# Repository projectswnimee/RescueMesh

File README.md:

<div align="center">

# RescueMesh

**ESP32 and LoRa emergency messaging for flood and disaster response**

**Semi-finalist — SL IoT competition, Sri Lanka**

</div>

<p align="center">
  
  <br>
  <sub>Original prototype photograph supplied by project collaborator Nimesha Nanayakkara. Click to view full size.</sub>
</p>

RescueMesh explores how battery-powered nodes can exchange SOS messages when
normal connectivity is unavailable. ESP32 controllers communicate through
AS32-TTL-100 LoRa radios, with progressive experiments covering broadcast,
relay forwarding, duplicate suppression, TTL and gateway uploads.

This is Nimesha Nanayakkara's maintained copy of the collaborative project.
The [original team repository](https://github.com/HiranGeeth/RescueMesh-Disaster-Rescue_Long-Range-Communication-System),
original MIT licence and hardware-author credits are preserved through explicit
[source attribution](ATTRIBUTION.md).

## System overview

```text
SOS button / Bluetooth input
            ↓
ESP32 field node ↔ LoRa relay nodes ↔ gateway receiver
                                           ↓
                                  Wi-Fi → test backend

Power-path PCB + battery supply + enclosure support the node hardware.
```

The checked-in firmware implements custom messaging over LoRa modules.
An operational LoRaWAN network server and LoRaWAN compliance are not demonstrated.

## Included implementation

| Area | Source and assets |
|---|---|
| Firmware experiments | [test_codes/](test_codes/) — UART, parameter configuration, point-to-point and broadcast messaging |
| Relay behaviour | Deduplication, time windows, TTL, randomized retransmission and rebroadcast tests |
| User interaction | SOS button handling and Bluetooth-to-node experiments |
| Gateway integration | LoRa reception and Wi-Fi upload to a configurable test endpoint |
| Power electronics | [Power-path circuit](hardware/Power%20Path%20Management%20Circuit/) — KiCad schematic/PCB, circuit image and fabrication PDFs |
| Mechanical design | [Enclosure](hardware/Enclosure/) — Blender, STL, Cura and printer-specific G-code assets |
| Coverage studies | [MATLAB simulations](matlab_simulations/) — terrain, coverage and routing experiments |

## Hardware design previews

<p align="center">

</p>

These are design assets. The power-path and enclosure documentation credits
**Lasindu Viduranga**. The photograph above documents the assembled prototype;
calibrated power measurements and repeatable field-range data still need to
be added with their test conditions.

## Getting started

1. Clone this repository:

   ```bash
   git -c core.longpaths=true clone https://github.com/projectswnimee/RescueMesh.git
   ```

2. Use Arduino IDE with the ESP32 board support installed. Choose the board
   matching your ESP32 development module.
3. Start with [the GPIO/UART test](test_codes/Code_1.0_GPIO_UART_Test/1.0_GPIO_UART_Test.ino).
   Read the selected sketch's pin definitions before connecting the radio.
4. Progress through parameter read/write and point-to-point tests before using
   relay or field-node sketches. Match radio channel and air settings at both ends.
5. For the gateway upload test, copy
   [secrets.example.h](test_codes/Code_1.3.2.1_Gateway_Backend_Upload_Test/Reciever_Code/secrets.example.h)
   to `secrets.h` in the same sketch folder and enter your own Wi-Fi and endpoint
   values. That local file is ignored by Git.
6. Record the sketch, board package version, wiring, settings and serial logs
   with each experiment. Test one transmitter/receiver pair before adding relays.

The original directories and sketch filenames are retained for traceability.
Arduino IDE may offer to create a matching sketch folder for older filenames.

For `matlab_simulations/DEM.m`, set `OPENTOPOGRAPHY_API_KEY` in your local
environment if downloading new terrain data. Do not commit or print the key.

## Evidence and limits

- **Competition:** semi-finalist in the SL IoT competition, Sri Lanka, reported
  by project collaborator Nimesha Nanayakkara. The edition/year and official
  certificate or announcement are pending addition; see [attribution](ATTRIBUTION.md).
- **Radio:** range and power depend on antennas, configuration, environment and
  board design. Source claims such as 3 km or microamp sleep current are not
  presented here as independently measured whole-system results.
- **Security:** the field-node sketch contains a public demonstration key
  whitelist. This does not establish cryptographic authentication or confidentiality;
  an upstream filename containing “Encryption” is not evidence of secure encryption.
- **Readiness:** folder names such as `Production_Firmware` are inherited source
  labels. This copy has not been newly tested on physical hardware, and is not
  a certified emergency-response system.
- **Simulation:** terrain inputs and MATLAB outputs need their own provenance
  and validation; a coverage simulation does not establish field coverage.

## Collaboration and licence

Use branches and pull requests for new contributions. State your engineering
role and attach relevant measurements or design files. Uploading the shared
source does not confer sole authorship of the project.

See [ATTRIBUTION.md](ATTRIBUTION.md) for the source revision, documented
contributors and publication changes. The original [MIT licence](LICENSE)
and its copyright notice are retained unchanged.

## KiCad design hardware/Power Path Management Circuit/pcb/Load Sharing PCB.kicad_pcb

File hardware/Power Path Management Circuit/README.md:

# 🔋 Power Path Management Circuit  
## LiPo Charger + Boost Converter with Load Sharing (5V Output)

---

## 📌 Description
This module implements a **power path management system** that allows a device (e.g., Arduino, ESP32) to be powered while simultaneously charging a LiPo battery.

### ✅ Key Features
- Safe battery charging  
- Automatic load sharing between USB input and battery  
- Stable 5V output using a boost converter  

---

## ⚙️ How It Works
- The **TP4056 module** charges the LiPo battery from a 5V USB input  
- A **P-channel MOSFET (DMP1045U)** controls power flow  

### 🔌 Operation Modes
**When USB is connected:**
- Load is powered directly from USB  
- Battery charges simultaneously  

**When USB is disconnected:**
- Battery supplies power to the load  

- The **MT3608 boost converter** steps battery voltage up to a stable **5V output**

---

## 🧩 Components Used
- TP4056 LiPo Charger Module (with protection)  
- LiPo Battery (3.7V)  
- DMP1045U P-Channel MOSFET  
- SB220 Schottky Diode  
- 10kΩ Resistor  
- MT3608 Boost Converter Module  

---

## 📁 Files Included
- **schematics/** → Circuit diagram files  
- **pcb/** → PCB design files (Gerber, layout)  

---

## 🔌 Input & Output
- **Input:** 5V (USB)  
- **Battery:** 3.7V LiPo  
- **Output:** Regulated 5V  

---

## ⚠️ Notes
- Adjust **Rprog** on TP4056 to set charging current  
- Adjust **MT3608** to get exact 5V output before connecting load  
- Ensure proper heat dissipation for high current usage  

---

## 🧠 Applications
- Arduino & Embedded Systems  
- Portable electronics  
- IoT devices with battery backup  

---

## 👨‍💻 Author
**Lasindu Viduranga**  
📧 wplvidu@gmail.com  

**Team Member**  
Rescue Mesh

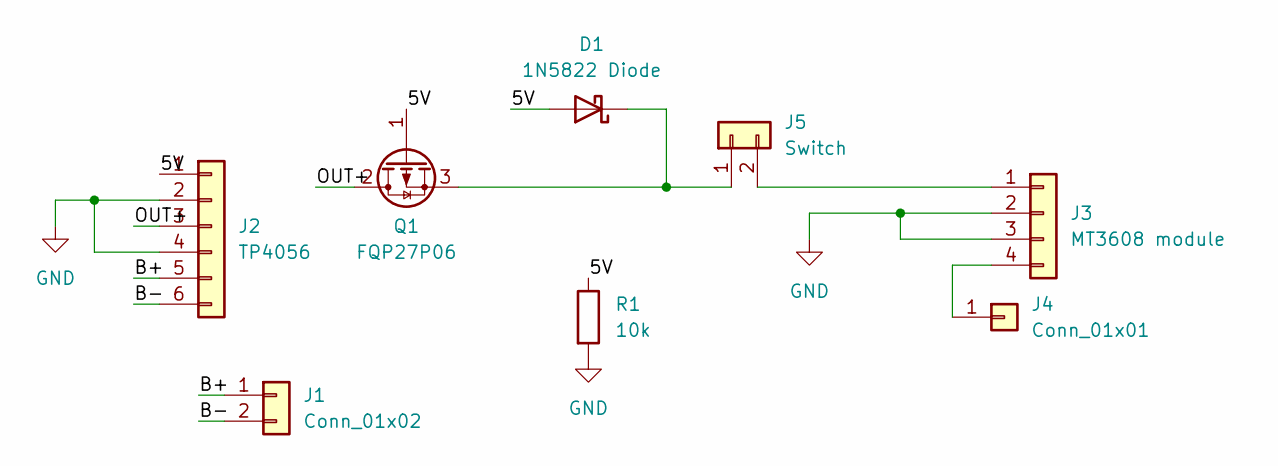
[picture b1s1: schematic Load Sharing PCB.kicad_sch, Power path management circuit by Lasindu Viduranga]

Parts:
D1: 1N5822 Diode; D_DO-201AD_P3.81mm_Vertical_AnodeUp
J1: Conn_01x02; PinHeader_1x02_P2.54mm_Vertical
J2: TP4056; TP4056-18650
J3: MT3608 module; MT3608_module
J4: Conn_01x01; PinHeader_1x01_P2.54mm_Vertical
J5: Switch; PinHeader_1x02_P2.54mm_Horizontal
Q1: FQP27P06; TO-220-3_Vertical
R1: 10k; R_Axial_DIN0207_L6.3mm_D2.5mm_P7.62mm_Horizontal

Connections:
/5V: D1.2 (A), J2.1, Q1.1 (G), R1.1
/B+: J1.1, J2.5
/B-: J1.2, J2.6
/OUT+: J2.3, Q1.2 (D)
GND: J2.2, J2.4, J3.2, J3.3, R1.2
unnamed: D1.1 (K), J5.1, Q1.3 (S)
unnamed: J3.1, J5.2
unnamed: J3.4, J4.1

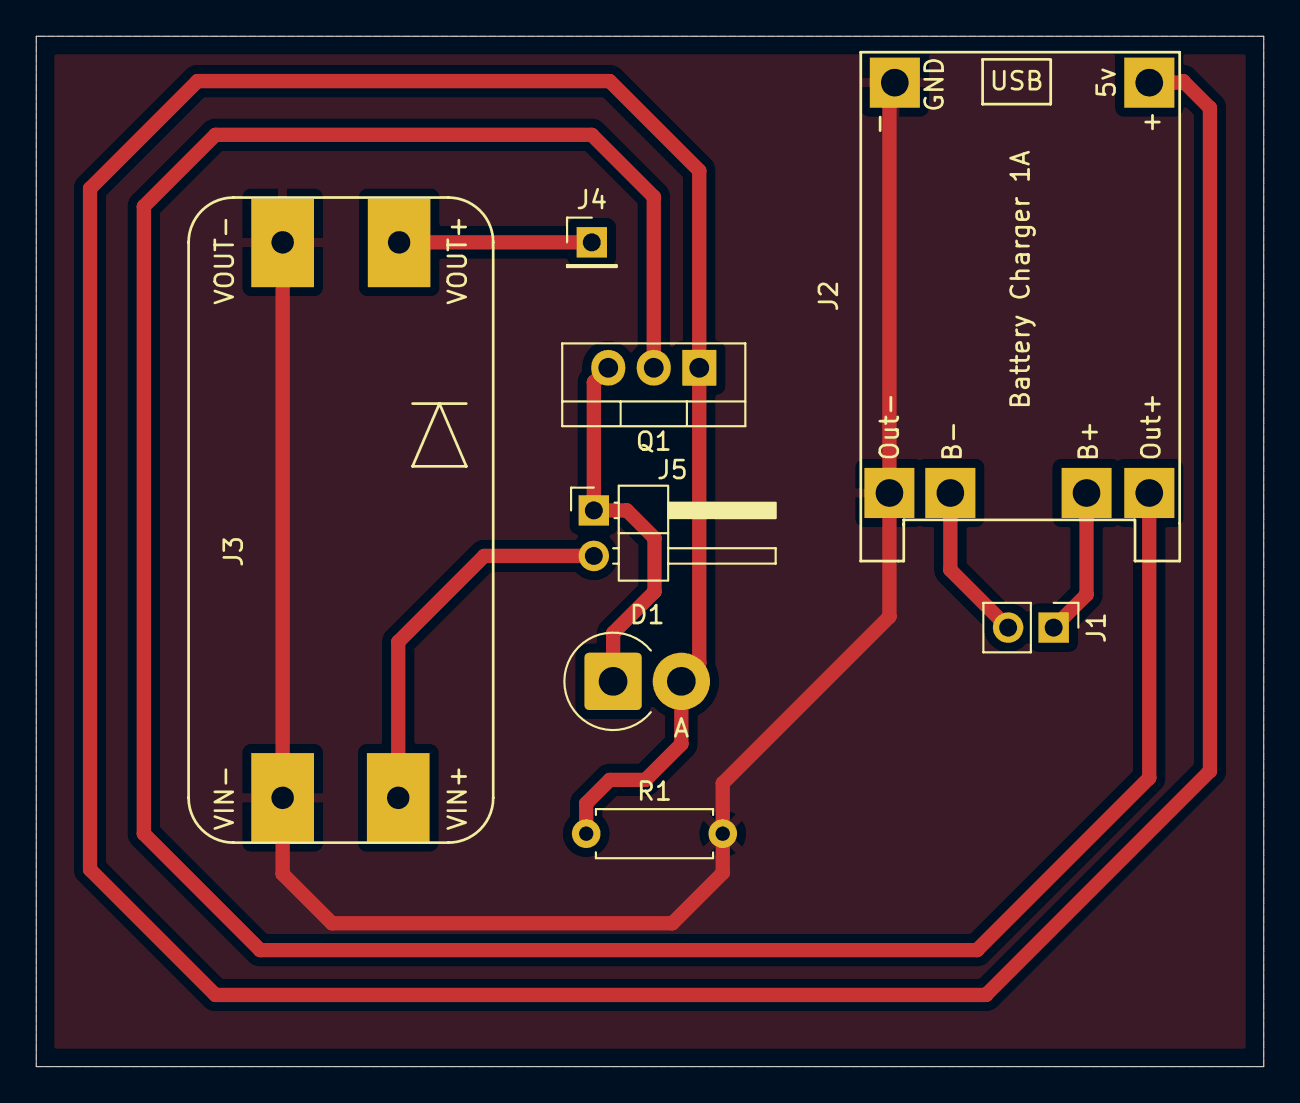
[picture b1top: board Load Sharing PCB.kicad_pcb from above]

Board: 2 copper layers, 68.5 x 57.5 mm, 8 parts (0 on the bottom side), 8 nets.

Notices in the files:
README.md:
License: MIT
